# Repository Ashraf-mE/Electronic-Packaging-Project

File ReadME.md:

# Electrocardiograph (ECG) Circuit Design

This repository contains the schematic and PCB designs of an Electrocardiograph (ECG) circuit, created using **EasyEDA** and **Eagle** software as part of the Electronic Packaging Assignment.

## Objective
Designing the layout, schematic, and PCB of an ECG circuit using **EasyEDA** and **Eagle** software.

## Components Used
- **ICs**: AD620, ISO124, LF412CN, OP97AP
- **Capacitors**: 0.1 µF, 0.47 µF, 1 µF
- **Resistors**: 10kΩ, 1kΩ, 50kΩ, 47kΩ, 3.2kΩ, 32kΩ, 5.6MΩ, 24kΩ
- **Switches**: DIP switch (EL04)
- **Other Components**: TBlock-M4, Voltage Supply Pins (HDR-2.54 WS-5P)

## Screenshots
#### Circuit

#### Schematic

#### Common Layers

## Design Tools
### 1. EasyEDA
- **Schematic Design**
- **PCB Design** (2D and 3D views)

### 2. Eagle Autodesk
- **Schematic Design**
- **PCB Design**

## PCB Design Details
| Feature                      | EasyEDA (mm)  | Eagle (mm) |
|------------------------------|---------------|------------|
| **Board Width**               | 84.24         | 80.95      |
| **Board Height**              | 90.297        | 86.35      |
| **Board Area**                | 7606.62 Sq.   | 6990.03 Sq.|
| **Copper Layers**             | 2             | 2          |
| **Board Thickness**           | 1.6           | 1.57       |
| **Via Drill Size**            | 0.305         | 0.35       |
| **Min. Copper Trace Width**   | 0.254         | 0.15       |
| **Max. Drill Size**           | 1.00          | 1.10       |
| **Min. Drill Size**           | 0.305         | 0.35       |
| **ERC & DRC Errors**          | 0             | 0          |

## Contributions
- **Pamidi Mohammad Ashraf**:
  - Designed schematic in Eagle
  - Designed PCB in EasyEDA
- **Gowtham N**:
  - Designed schematic in EasyEDA
  - Designed PCB in Eagle

## Concepts & Improvisations
- **Multilayer PCB**: Two copper layers (top and bottom) with Vias for interconnections.
- **Double-sided PCB**: Components placed on both sides to minimize the circuit area.
- **Level 2 Packaging**: Single PCB board with Level 2 interconnections between components and ICs.

## Achievements
- Designed a multilayer (two-layer copper) PCB with zero **ERC** and **DRC** errors.
- Gained experience in both **Eagle Autodesk** and **EasyEDA** software.

## Reference
- [Electrocardiograph Circuit Design Report](https://core.ac.uk/download/pdf/199199084.pdf)
"# Electronic-Packaging-Project"

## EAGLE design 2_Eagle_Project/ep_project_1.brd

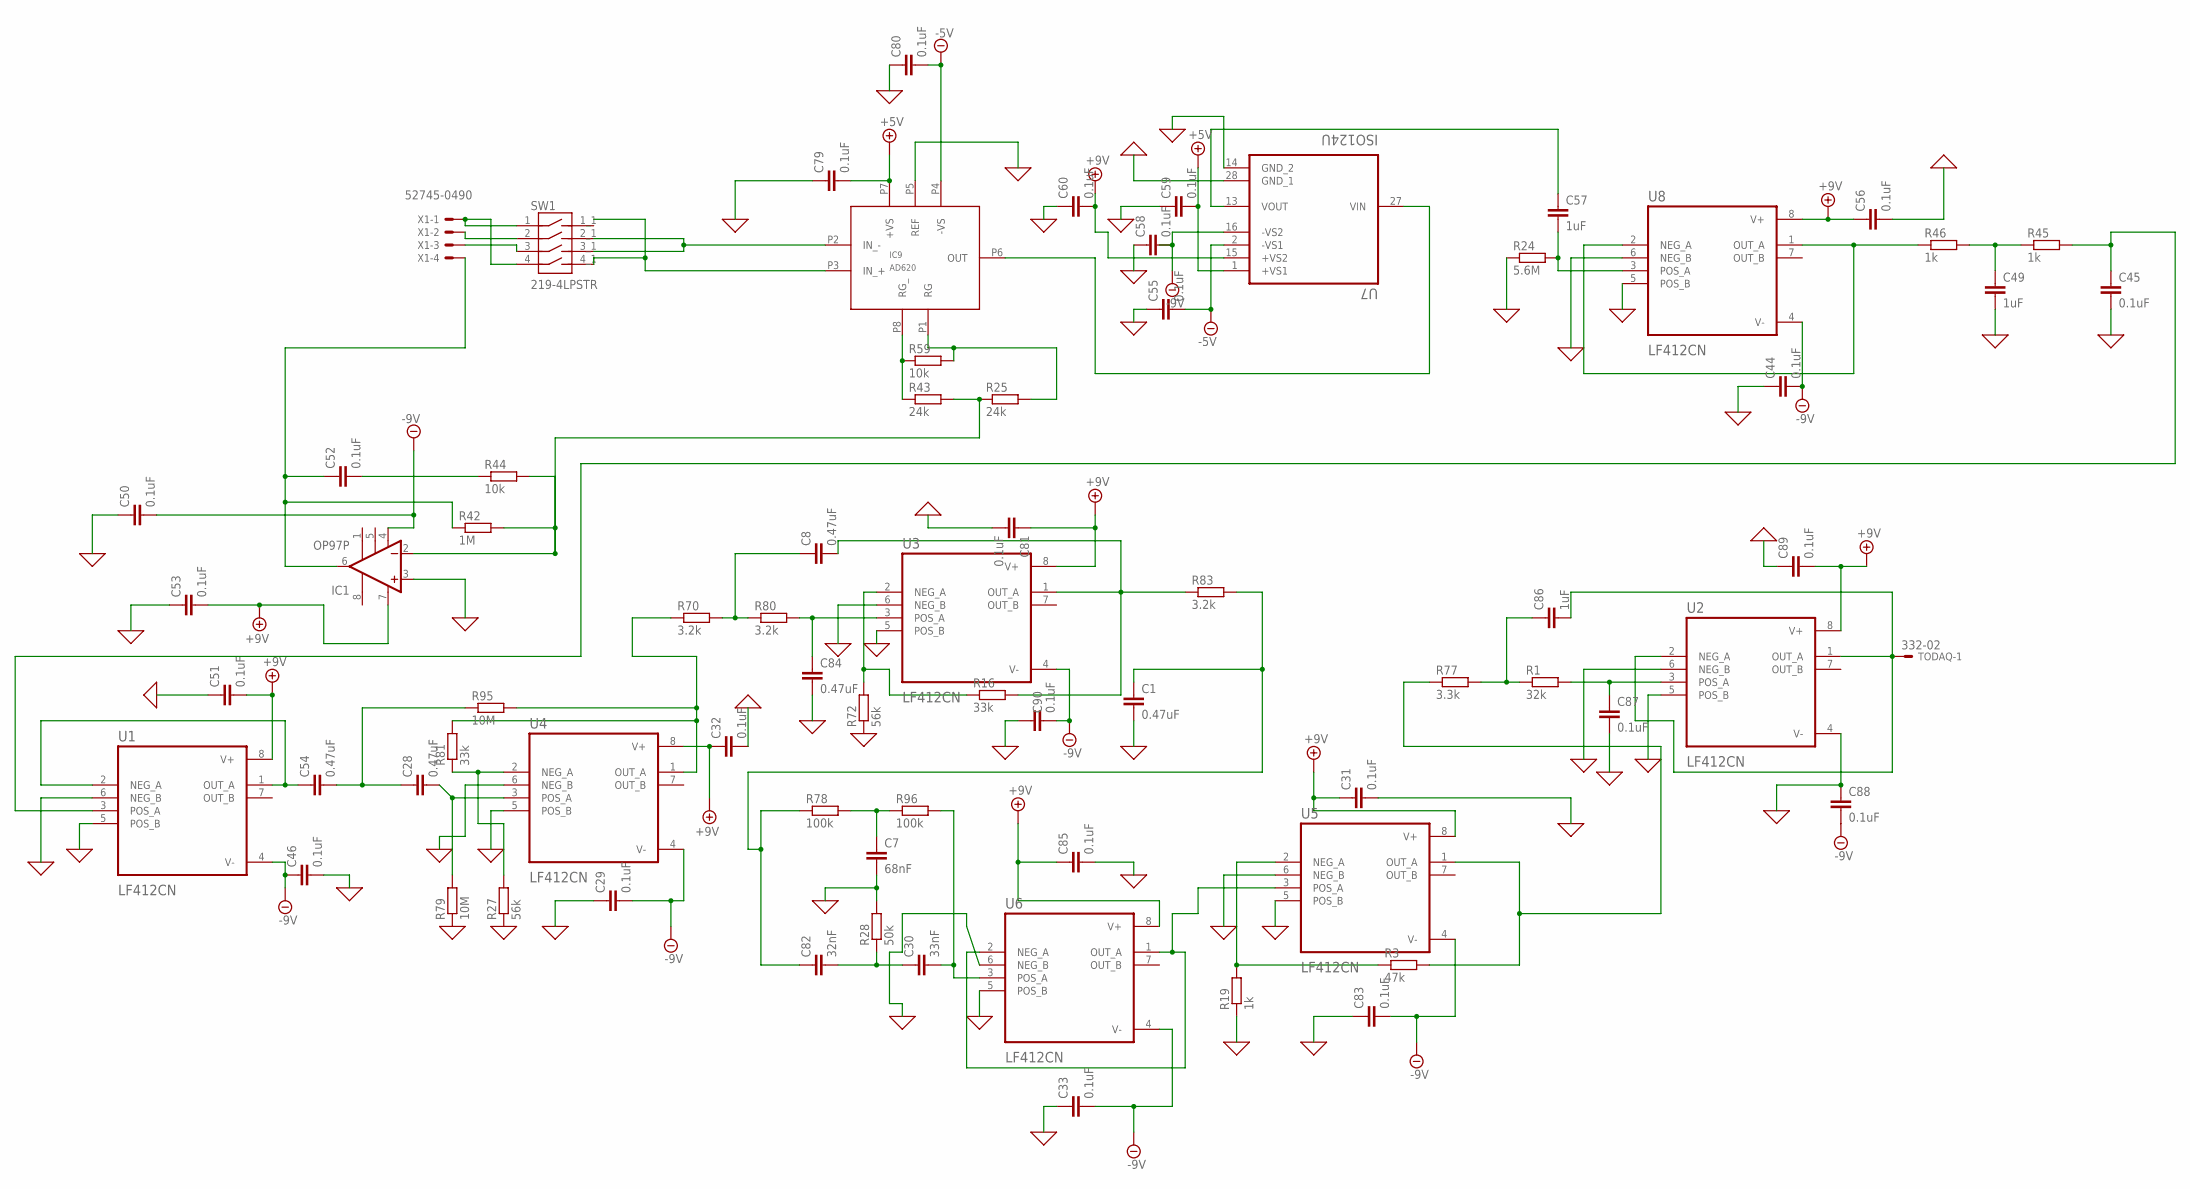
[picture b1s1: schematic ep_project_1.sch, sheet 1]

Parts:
C1, C8, C28, C54, C84: 0.47uF; C025-025X050
C7: 68nF; C025-025X050
C29, C31, C32, C33, C44, C45, C46, C50, C51, C52, C53, C55, C56, C58, C59, C60, C79, C80, C81, C83, C85, C87, C88, C89, C90: 0.1uF; C025-025X050
C30: 33nF; C025-025X050
C49, C57, C86: 1uF; C025-025X050
C82: 32nF; C025-025X050
IC1: OP97P; DIL08
IC9: AD620; DIL8
R1: 32k; 0204/7
R3: 47k; 0204/7
R16: 33k; VTA55
R19, R45, R46: 1k; 0204/7
R24: 5.6M; 0204/7
R25, R43: 24k; 0204/7
R27, R72: 56k; 0204/7
R28: 50k; 0204/7
R42: 1M; 0204/7
R44, R59: 10k; 0204/7
R70, R80, R83: 3.2k; 0204/7
R77: 3.3k; 0204/7
R78, R96: 100k; 0204/7
R79, R95: 10M; 0204/7
R81: 33k; 0204/7
SW1: 219-4LPSTR; SW_219-4LPSTR
TODAQ: 332-02
U1, U2, U3, U4, U5, U6, U8: LF412CN; DIP794W45P254L959H508Q8
U7: ISO124U; SOIC127P1033X265-8N
X1: 52745-0490

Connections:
0: C1.2, C7.2, C29.1, C31.2, C32.2, C33.1, C44.1, C45.2, C46.2, C49.2, C50.1, C51.1, C53.1, C55.1, C56.2, C58.1, C59.1, C60.1, C79.1, C80.1, C81.2, C83.1, C84.2, C85.2, C87.2, C88.1, C89.1, C90.1, IC1.3 (+IN), IC9.P5 (REF), R19.1, R24.1, R27.1, R28.2, R72.1, R79.1, U1.5 (POS_B), U1.6 (NEG_B), U2.4 (V-), U2.5 (POS_B), U2.6 (NEG_B), U3.5 (POS_B), U3.6 (NEG_B), U4.5 (POS_B), U4.6 (NEG_B), U5.5 (POS_B), U5.6 (NEG_B), U6.5 (POS_B), U6.6 (NEG_B), U7.14 (GND_2), U7.28 (GND_1), U8.5 (POS_B), U8.6 (NEG_B)
+5V: C59.2, C79.2, IC9.P7 (+VS), U7.1 (+VS1)
+9V: C31.1, C32.1, C51.2, C53.2, C56.1, C60.2, C81.1, C85.1, C89.2, IC1.7 (V+), U1.8 (V+), U2.8 (V+), U3.8 (V+), U4.8 (V+), U5.8 (V+), U6.8 (V+), U7.15 (+VS2), U8.8 (V+)
-5V: C55.2, C80.2, IC9.P4 (-VS), U7.2 (-VS1)
-9V: C29.2, C33.2, C44.2, C46.1, C50.2, C58.2, C83.2, C88.2, C90.2, IC1.4 (V-), U1.4 (V-), U3.4 (V-), U4.4 (V-), U5.4 (V-), U6.4 (V-), U7.16 (-VS2), U8.4 (V-)
unnamed: R3.2, R77.1, U5.1 (OUT_A)
unnamed: C45.1, R45.2, U1.3 (POS_A)
unnamed: IC9.P8 (RG_), R43.1, R59.1
unnamed: C52.2, R44.1
unnamed: IC1.2 (-IN), R25.1, R42.2, R43.2, R44.2
unnamed: C28.2, R79.2, U4.3 (POS_A)
unnamed: C28.1, C54.2, R95.1
unnamed: R27.2, R81.1, U4.2 (NEG_A)
unnamed: C30.2, R96.2, U6.3 (POS_A)
unnamed: C1.1, C82.1, R78.1, R83.2
unnamed: C7.1, R78.2, R96.1
unnamed: IC9.P6 (OUT), U7.27 (VIN)
unnamed: C30.1, C82.2, R28.1
unnamed: U5.3 (POS_A), U6.1 (OUT_A), U6.2 (NEG_A)
unnamed: R3.1, R19.2, U5.2 (NEG_A)
unnamed: C49.1, R45.1, R46.2
unnamed: C8.1, R70.2, R80.1
unnamed: C84.1, R80.2, U3.3 (POS_A)
unnamed: R16.1, R72.2, U3.2 (NEG_A)
unnamed: C86.1, R1.1, R77.2
unnamed: IC9.P3 (IN_+), SW1.4_1
unnamed: IC9.P2 (IN_-), SW1.2_1, SW1.3_1
unnamed: IC9.P1 (RG), R25.2, R59.2
unnamed: SW1.1, SW1.4, X1.1
unnamed: C57.1, U7.13 (VOUT)
unnamed: C8.2, R16.2, R83.1, U3.1 (OUT_A)
unnamed: C87.1, R1.2, U2.3 (POS_A)
unnamed: SW1.3, X1.3
unnamed: C54.1, U1.1 (OUT_A), U1.2 (NEG_A)
unnamed: SW1.2, X1.2
unnamed: R70.1, R81.2, R95.2, U4.1 (OUT_A)
unnamed: C52.1, IC1.6 (OUT), R42.1, X1.4
unnamed: C57.2, R24.2, U8.3 (POS_A)
unnamed: R46.1, U8.1 (OUT_A), U8.2 (NEG_A)
unnamed: C86.2, TODAQ.1, U2.1 (OUT_A), U2.2 (NEG_A)

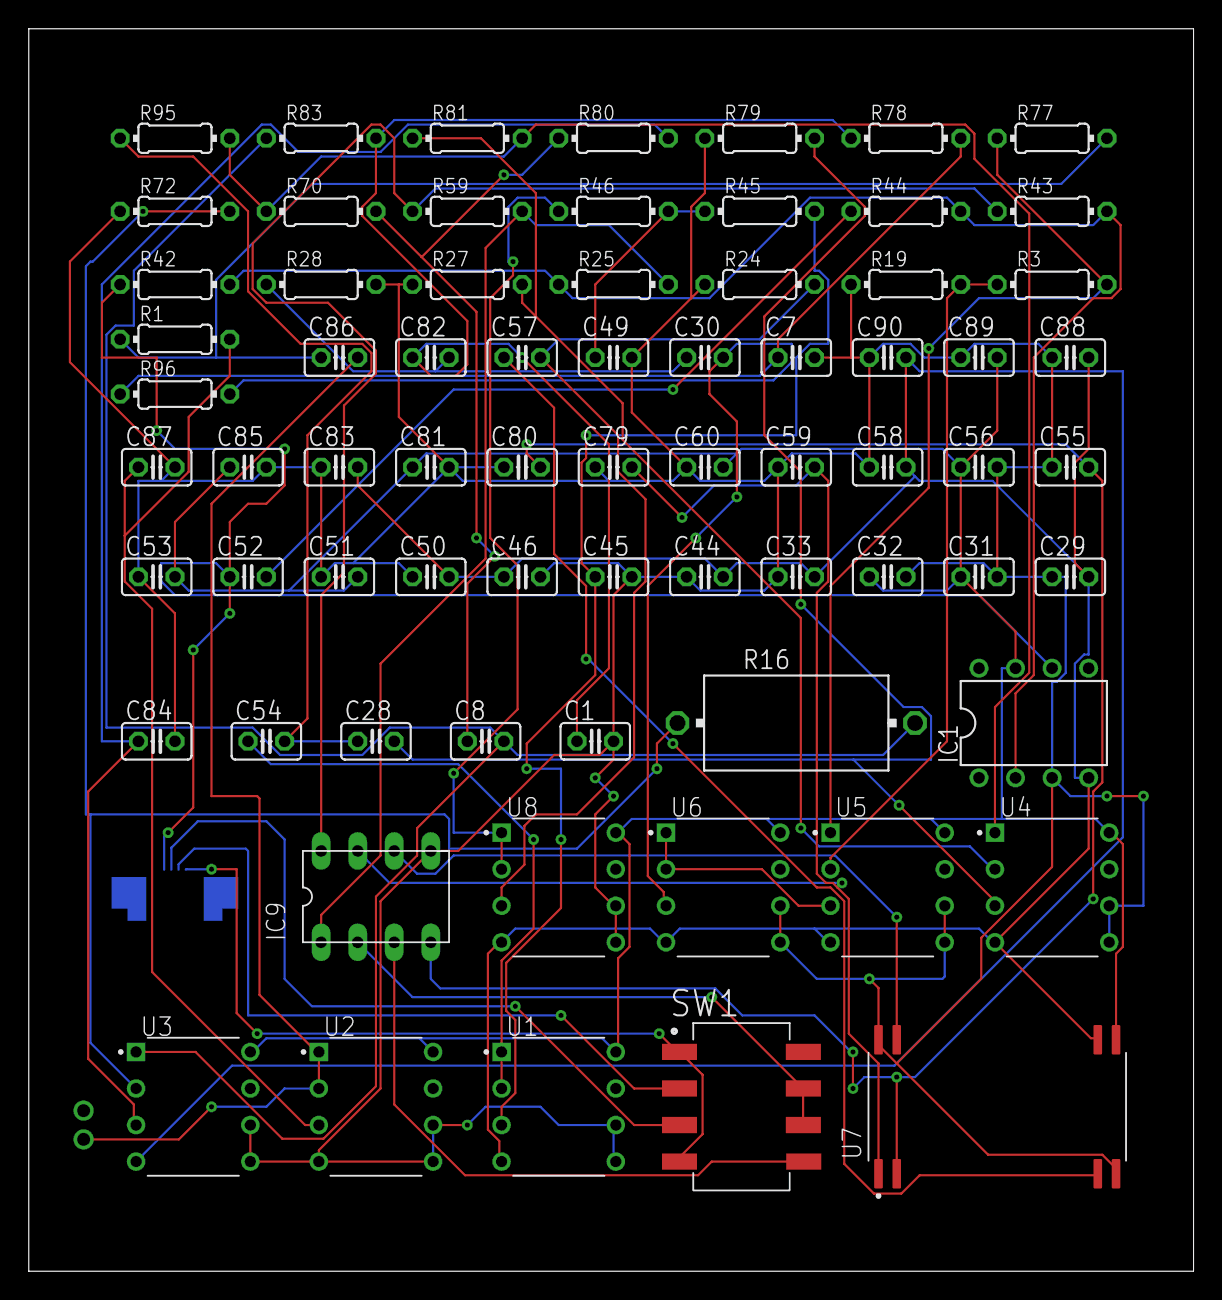
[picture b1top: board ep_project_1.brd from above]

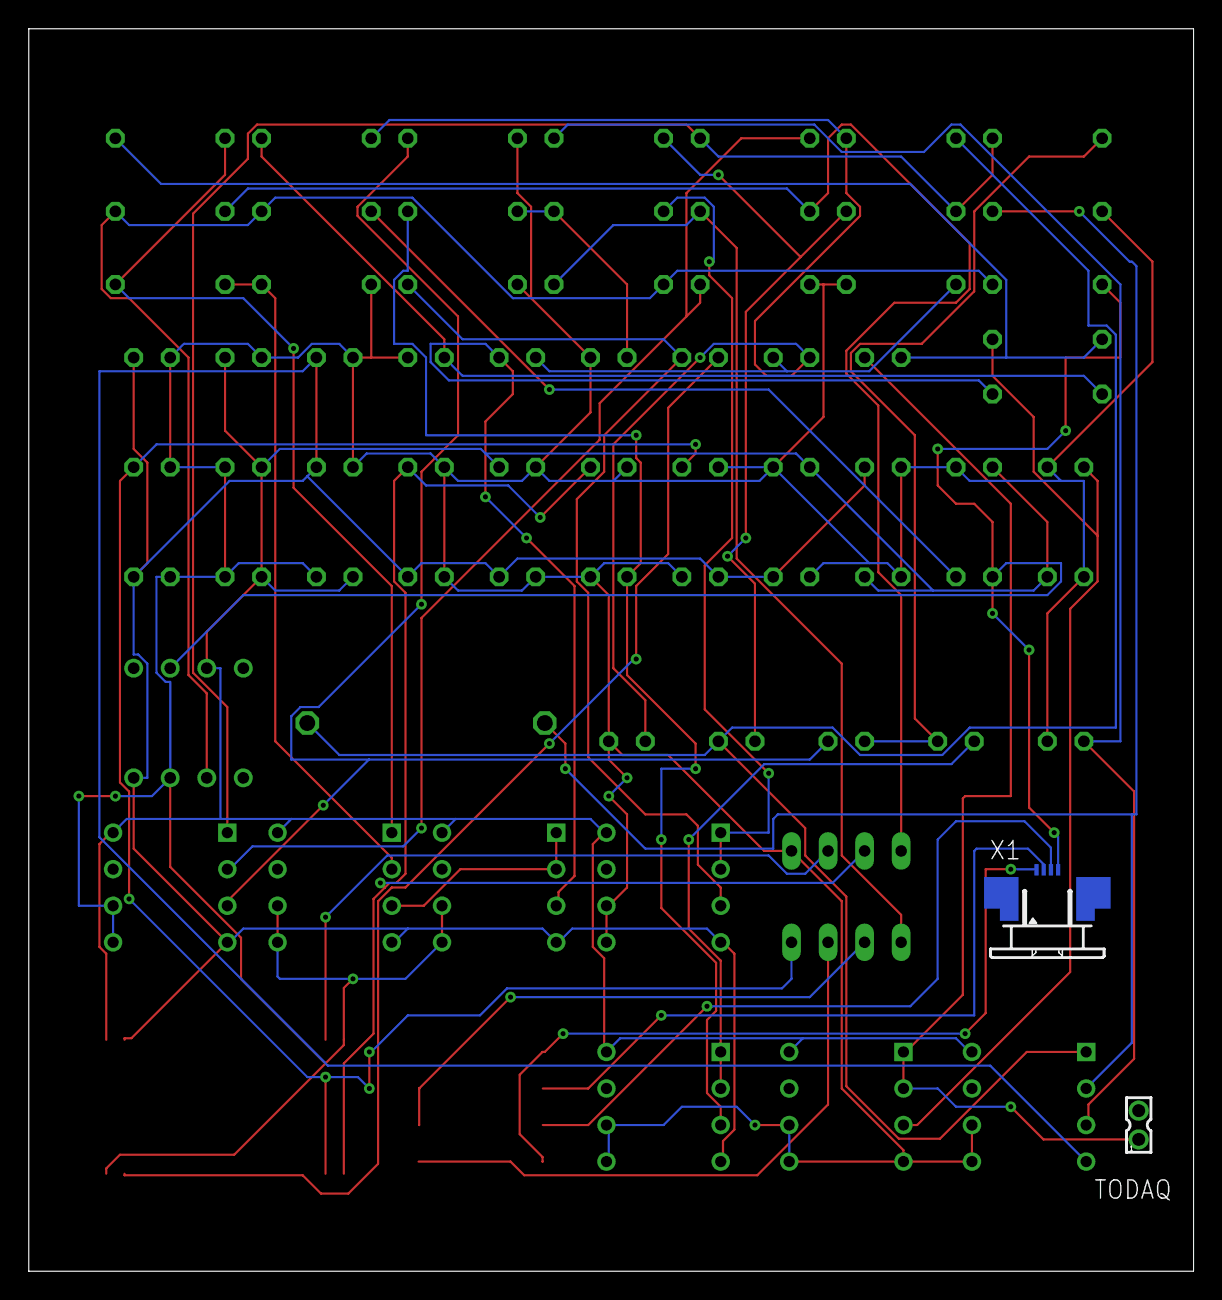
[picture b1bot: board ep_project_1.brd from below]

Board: 2 copper layers, 81.0 x 86.3 mm, 73 parts (2 on the bottom side), 40 nets.

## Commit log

2024-10-09 All files at once commited
